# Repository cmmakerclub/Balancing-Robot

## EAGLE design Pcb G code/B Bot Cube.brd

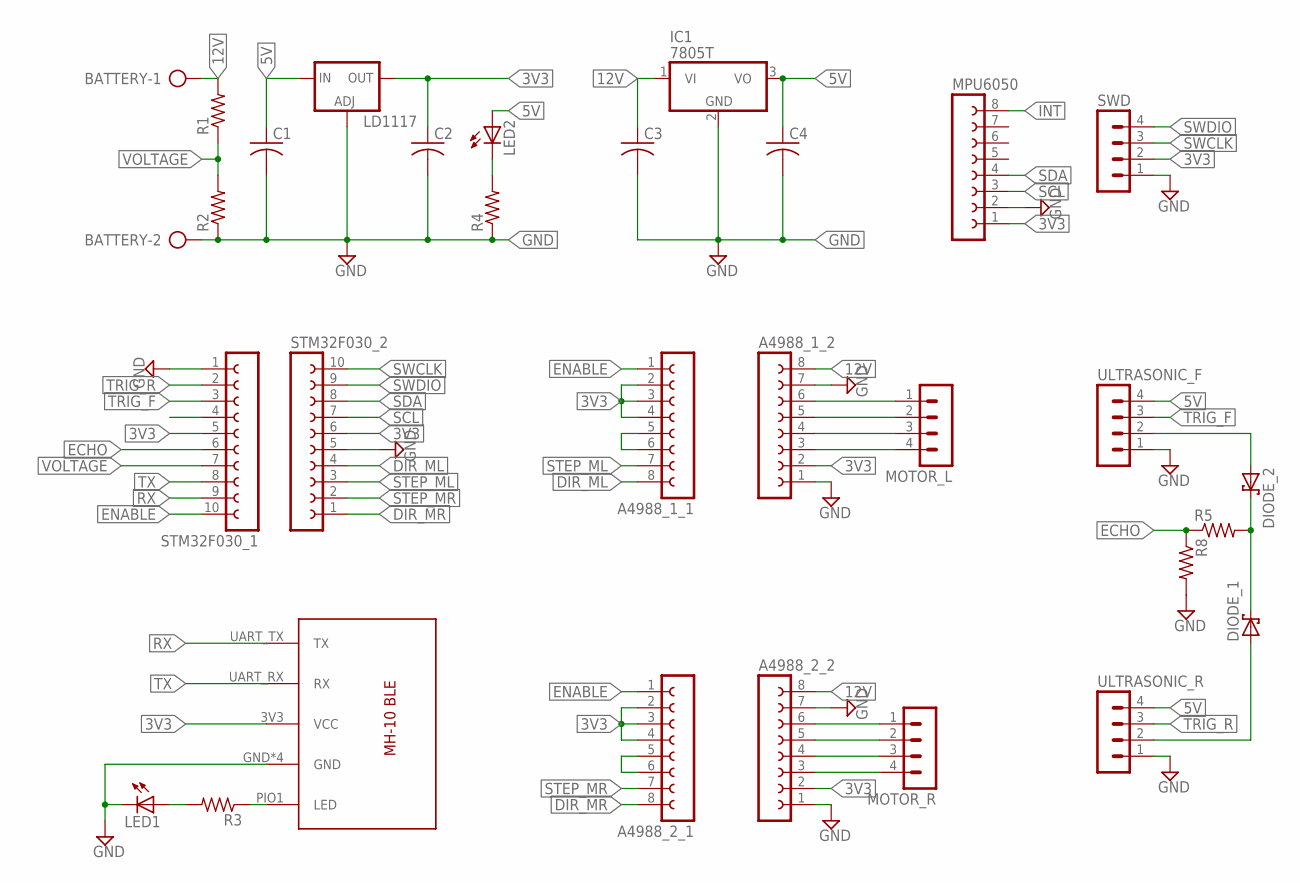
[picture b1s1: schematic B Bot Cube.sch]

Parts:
A4988_1_1, A4988_1_2, A4988_2_1, A4988_2_2: FE08-1; FE08
BATTERY: AK500/2
C1, C2, C3, C4: C-USC0805K; C0805K
DIODE_1, DIODE_2: BAT60J; SOD323_ST
IC1: 7805T; TO220H
LD1117: LD117AS33TR; SOT223
LED1, LED2: LED-0805; LED-805
MOTOR_L: MA04-1
MOTOR_R: MA04-1
MPU6050: FE08-1; FE08
R1, R2, R3, R4, R5, R8: R-US_M0805; M0805
STM32F030_1, STM32F030_2: FE10-1; FE10
SWD: MA04-1
U$1: HM-10
ULTRASONIC_F: MA04-1
ULTRASONIC_R: MA04-1

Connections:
3V3: A4988_1_1.2, A4988_1_1.3, A4988_1_1.4, A4988_1_2.2, A4988_2_1.2, A4988_2_1.3, A4988_2_1.4, A4988_2_2.2, C2.1, LD1117.4 (OUT), MPU6050.1, STM32F030_1.5, STM32F030_2.6, SWD.2, U$1.3V3 (VCC)
5V: C1.1, C4.1, IC1.3 (VO), LD1117.3 (IN), LED2.A, ULTRASONIC_F.4, ULTRASONIC_R.4
12V: A4988_1_2.8, A4988_2_2.8, BATTERY.1, C3.1, IC1.1 (VI), R1.2
DIR_ML: A4988_1_1.8, STM32F030_2.4
DIR_MR: A4988_2_1.8, STM32F030_2.1
ECHO: R5.1, R8.1, STM32F030_1.6
ENABLE: A4988_1_1.1, A4988_2_1.1, STM32F030_1.10
GND: A4988_1_2.1, A4988_1_2.7, A4988_2_2.1, A4988_2_2.7, BATTERY.2, C1.2, C2.2, C3.2, C4.2, IC1.2 (GND), LD1117.1 (ADJ), LED1.C, MPU6050.2, R2.1, R4.1, R8.2, STM32F030_1.1, STM32F030_2.5, SWD.1, U$1.GND, U$1.GND2 (GND), U$1.GND3 (GND), U$1.GND4 (GND), ULTRASONIC_F.1, ULTRASONIC_R.1
INT: MPU6050.8
unnamed: DIODE_1.A, ULTRASONIC_R.2
unnamed: DIODE_2.A, ULTRASONIC_F.2
unnamed: DIODE_1.C, DIODE_2.C, R5.2
unnamed: LED2.C, R4.2
unnamed: LED1.A, R3.2
unnamed: R3.1, U$1.PIO1 (LED)
unnamed: A4988_2_1.5, A4988_2_1.6
unnamed: A4988_2_2.6, MOTOR_R.1
unnamed: A4988_2_2.5, MOTOR_R.2
unnamed: A4988_2_2.4, MOTOR_R.3
unnamed: A4988_2_2.3, MOTOR_R.4
unnamed: A4988_1_2.6, MOTOR_L.1
unnamed: A4988_1_2.5, MOTOR_L.2
unnamed: A4988_1_2.4, MOTOR_L.3
unnamed: A4988_1_2.3, MOTOR_L.4
unnamed: A4988_1_1.5, A4988_1_1.6
RX: STM32F030_1.9, U$1.UART_TX (TX)
SCL: MPU6050.3, STM32F030_2.7
SDA: MPU6050.4, STM32F030_2.8
STEP_ML: A4988_1_1.7, STM32F030_2.3
STEP_MR: A4988_2_1.7, STM32F030_2.2
SWCLK: STM32F030_2.10, SWD.3
SWDIO: STM32F030_2.9, SWD.4
TRIG_F: STM32F030_1.3, ULTRASONIC_F.3
TRIG_R: STM32F030_1.2, ULTRASONIC_R.3
TX: STM32F030_1.8, U$1.UART_RX (RX)
VOLTAGE: R1.1, R2.2, STM32F030_1.7

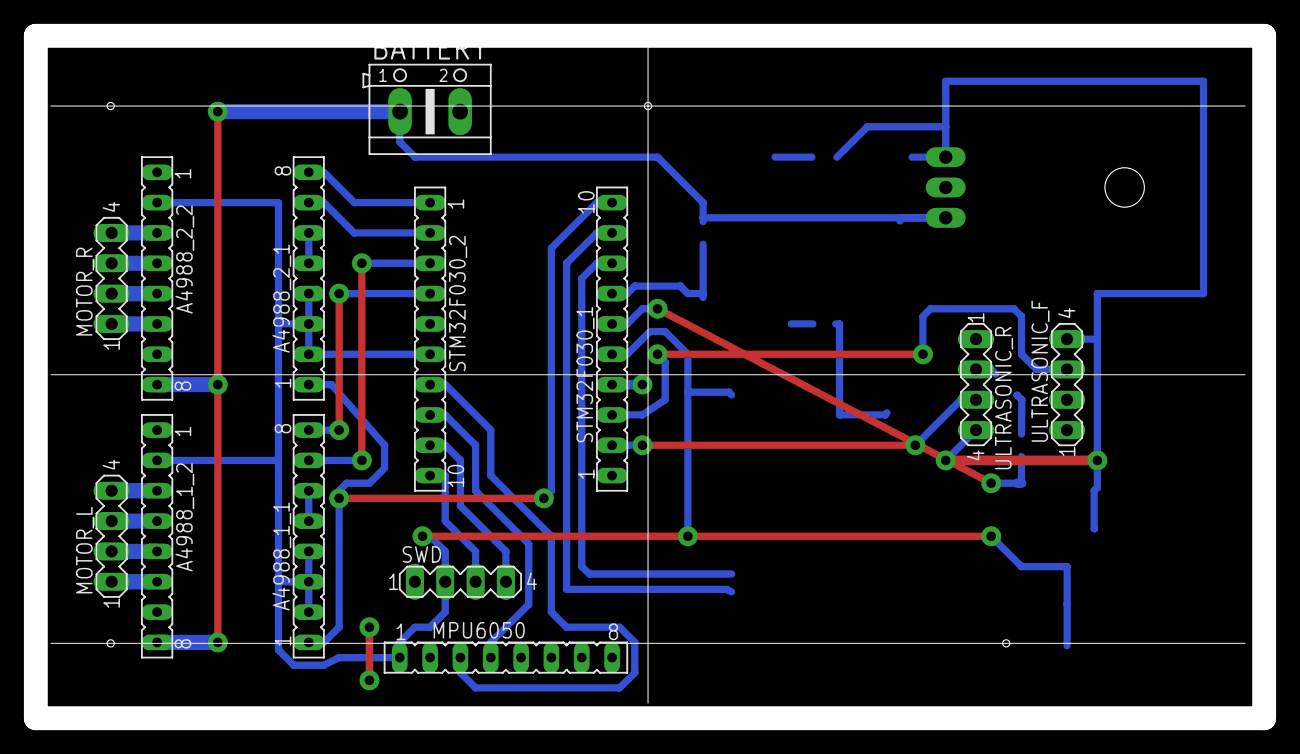
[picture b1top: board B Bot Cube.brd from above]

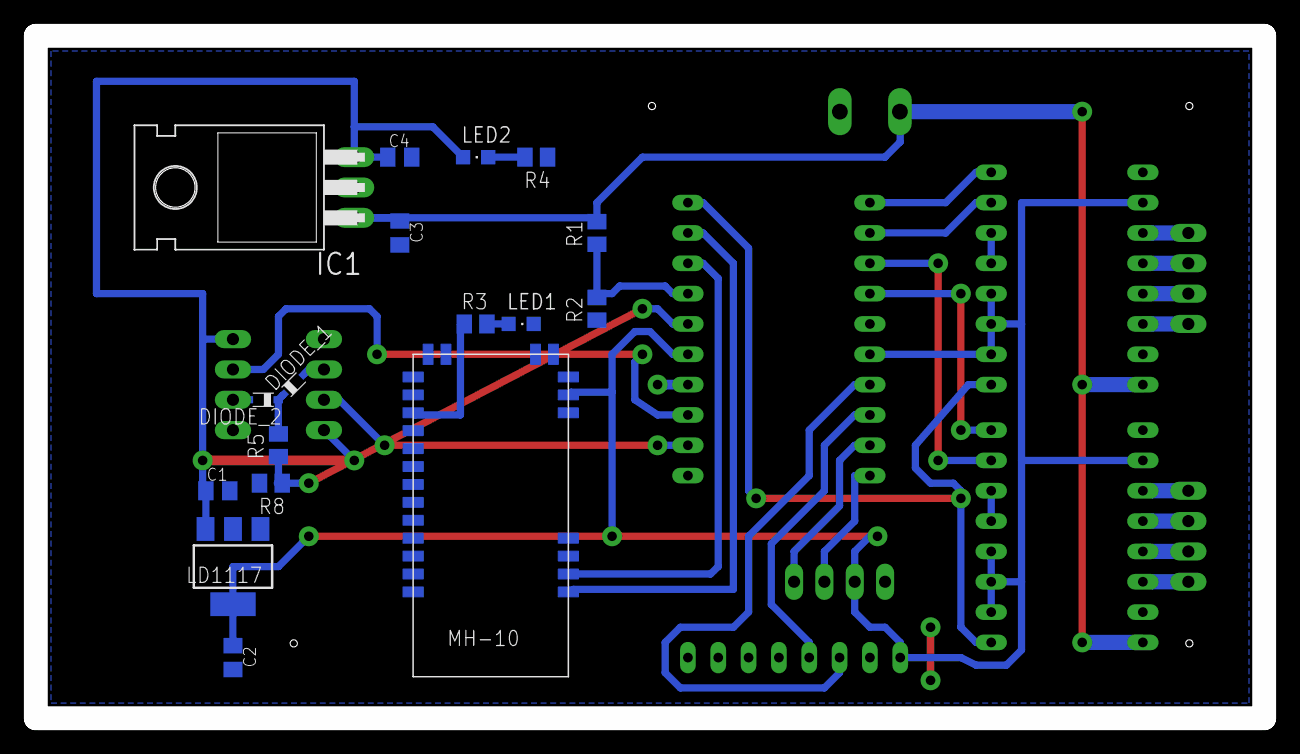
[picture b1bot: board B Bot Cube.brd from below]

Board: 2 copper layers, 102.9 x 57.2 mm, 30 parts (17 on the bottom side), 35 nets.

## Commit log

2014-12-29 add cad file
2014-12-29 update and add dwg files
2014-12-29 add G-code
2014-12-29 fixed bug
2014-12-30 add pcb g code
2014-12-31 start programming 31 12 14
2014-12-31 no message
2014-12-31 fixed 10us pulse
2014-12-31 imp distance measuring
2014-12-31 SR-04 OK
2014-12-31 add eagle add mxcube
2014-12-31 add delay before init mpu6050
2015-01-01 addsampling rate fixed Ahrs fixed i2c imp 10 uS
2015-01-01 imp adc
2015-01-01 decrease ahb apb bus
2015-01-02 a4988 ok direation ok
2015-01-02 two rank update a4988
2015-01-02 add controller
2015-01-03 decrease low limit speed
2015-01-03 add cascade control
2015-01-03 fixed init start
2015-01-03 save
2015-01-03 save before add dma
2015-01-03 add dma
2015-01-03 bug in control command >> velocity control over force to velocity control
2015-01-04 success in 1st version pi velocity control over pd angle control
2015-01-09 controller bug
2015-01-10 for system ID
2015-01-10 stable but wrong
2015-01-11 fixed
2015-01-11 add matlab LQR controller
2015-01-11 float >> double data
    remodeling position equation
2015-01-11 2nd version
2015-01-13 add Matlab file
2015-01-21 add slip cut
